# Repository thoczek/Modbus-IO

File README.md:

# Modbus-IO modules<br>

### Complete Modbus I/O modules on ATmega8<br>
### Contains:<br>
 - 4DI-4DO - 4 digital inputs 24VDC and 4 relay NO/NC outputs<br>
 - 8DI - 8 digital inputs 24VDC<br>
 - 7RO - 7 Relay outputs NO/NC<br>
 - WIFI - Module for WIFI conectibity for modules<br>
 - EAP-MODBUSconfig - Software for configuration of the modules.<br>
   Modules have possibility to act in TCP mode throught WIFi module.<br>

### Technology used:
Schematics and PCB board done in Kicad.<br>
Firmware - C++ eclipse. <br>
Software - C#

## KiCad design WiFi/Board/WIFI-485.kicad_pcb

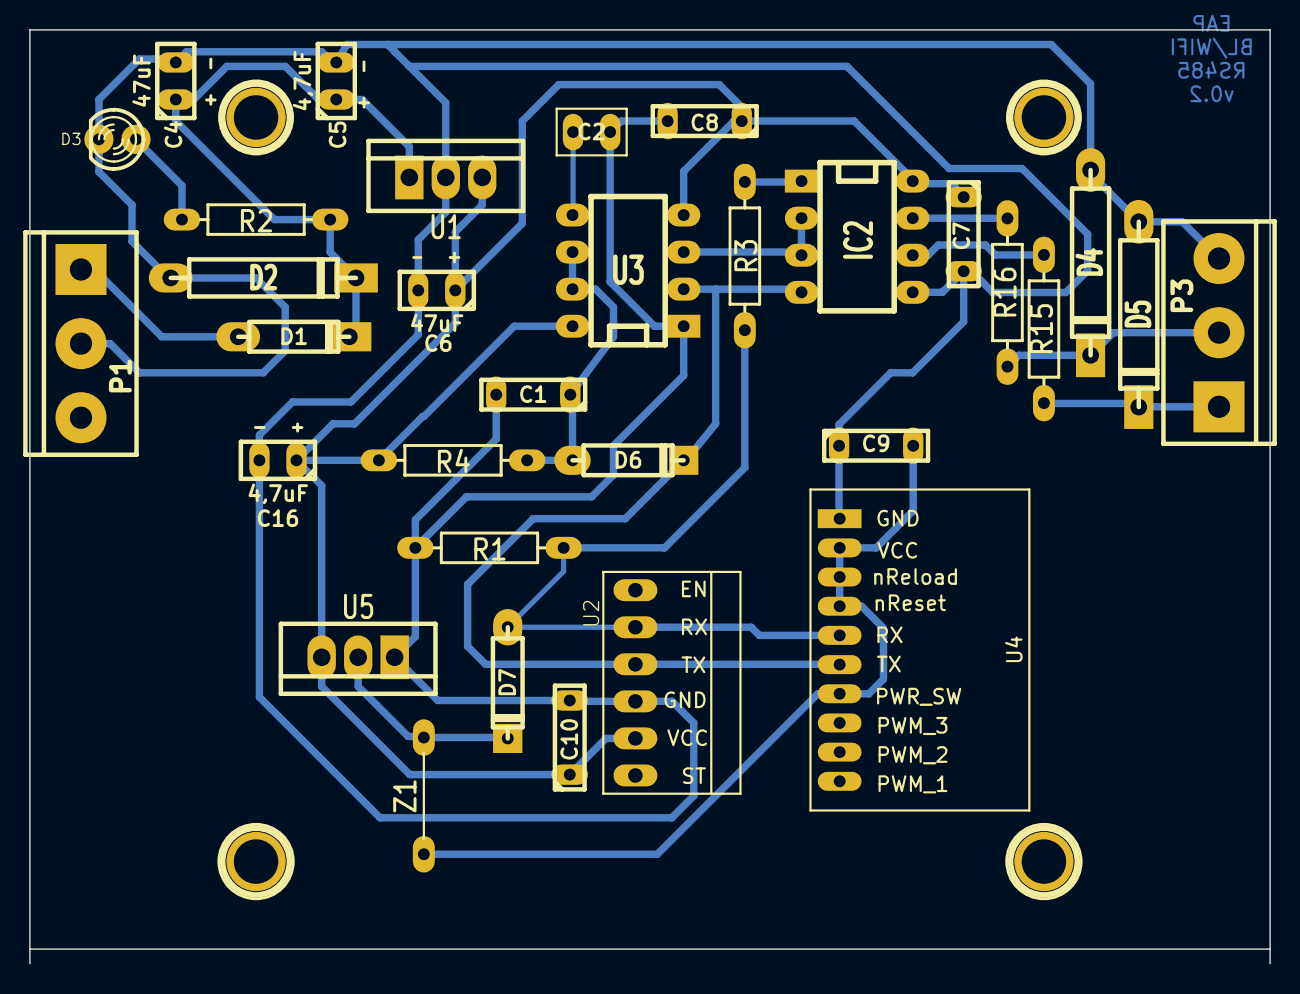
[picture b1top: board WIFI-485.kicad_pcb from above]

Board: 2 copper layers, 85.0 x 64.0 mm, 32 parts (0 on the bottom side), 17 nets.

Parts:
C1: 220nF; C-5
C2: 10nF; C-2_5
C4, C6: 47uF; C-2_5
C5, C16: 4,7uF; C-2_5
C7, C8, C9, C10: 100nF; C-5
D1: DIODE; D3-BOLD
D2: Tr_30V; D5-BOLD
D3: LED; LED-3MM
D4, D5: Tr_15V; D5-BOLD
D6, D7: 1N4148; D3-BOLD
IC2: ADM485; DIP-8__300_ELL
P1, P3: 3_PIN; bornier3
R1: 2k; R-10
R2: 3,9k; R-10
R3: 1_k; R-10
R4: 10k; R-10
R15, R16: 10R; R-10
U1: 7805
U2: HC-05
U3: NE555; DIP-8__300_ELL
U4: USR-WIFI232-T
U5: LD1117V33_; LD1117V33
Z1: Z

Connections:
+5V: C6.1, C7.1, C8.1, C10.1, C16.1, IC2.8, R4.1, U1.VO, U2.2, U3.4, U3.8, U5.3
A: IC2.6, R15.2
B: IC2.7, R16.2
DGND: C1.2, C2.2, C4.2, C5.2, C6.2, C7.2, C8.2, C9.1, C10.2, C16.2, D2.1, D3.2, D4.1, D5.1, IC2.5, P1.2, P3.3, R1.1, U1.GND, U2.3, U3.1, U4.1, U5.1
unnamed: C2.1, U3.5
unnamed: IC2.1, R3.2
unnamed: D6.2, IC2.4, U2.4, U3.2, U4.6
unnamed: IC2.2, IC2.3, U3.3
unnamed: D7.1, R1.2, R3.1, U2.5, U4.5
unnamed: D7.2, U5.2, Z1.1
unnamed: C1.1, D6.1, R4.2, U3.6, U3.7
unnamed: C9.2, U4.2, U4.3, U4.4, U4.7, Z1.2
unnamed: D4.2, P3.2, R16.1
unnamed: D5.2, P3.1, R15.1
unnamed: D1.1, P1.1
unnamed: D3.1, R2.2
VCC: C4.1, C5.1, D1.2, D2.2, R2.1, U1.VI

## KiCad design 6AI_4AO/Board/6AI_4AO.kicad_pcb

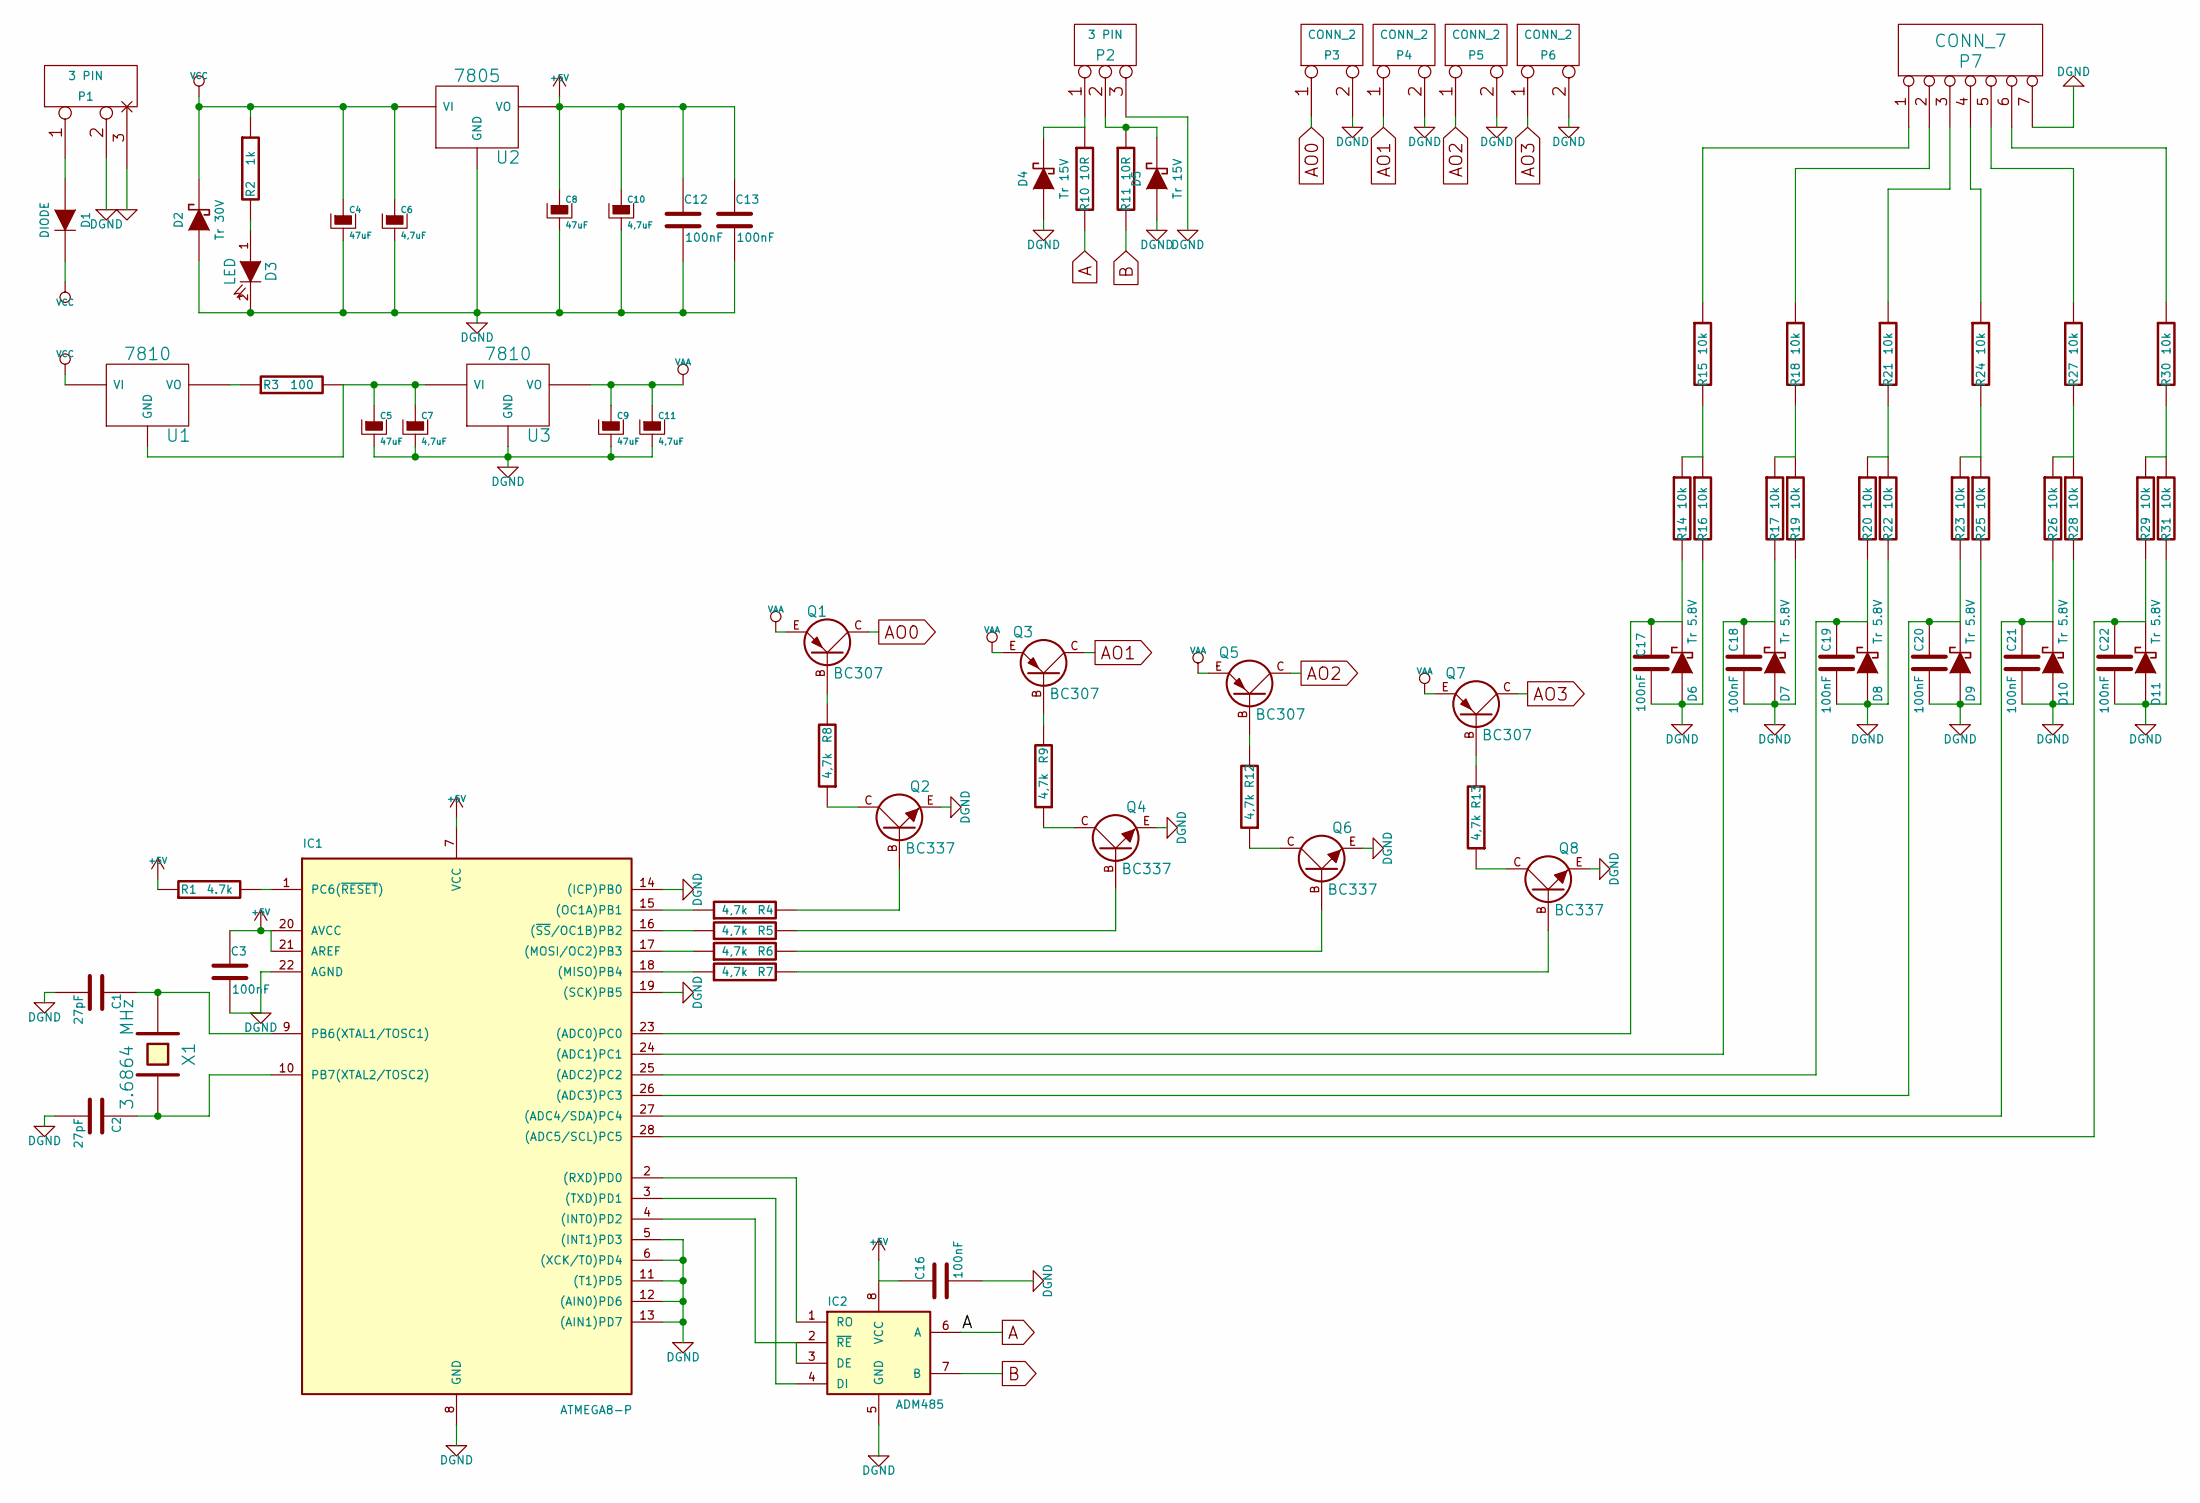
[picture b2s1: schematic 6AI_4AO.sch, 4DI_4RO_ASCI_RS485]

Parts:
C1, C2: 27pF; C-2_5
C3, C12, C13, C16, C17, C18, C19, C20, C21, C22: 100nF; C-5
C4, C5, C8, C9: 47uF; C-2_5
C6, C7, C10, C11: 4,7uF; C-2_5
D1: DIODE; D4-BOLD
D2: Tr 30V; D4-BOLD
D3: LED; LED-3MM
D4, D5: Tr 15V; D4-BOLD
D6, D7, D8, D9, D10, D11: Tr 5.8V; D4-BOLD
IC1: ATMEGA8-P; DIP-28_W7.62mm_LongPads
IC2: ADM485; DIP-8_W7.62mm_LongPads
P1, P2: 3 PIN; bornier3
P3, P4, P5, P6: CONN_2; bornier2
P7: CONN_7; bornier7
Q1, Q3, Q5, Q7: BC307; TO92_Moj
Q2, Q4, Q6, Q8: BC337; TO92_Moj
R1: 4.7k; R-7_62
R2: 1k; R-7_62
R3: 100; R-7_62
R4, R5, R6, R7, R8, R9, R12, R13: 4,7k; R-7_62
R10, R11: 10R; R-7_62
R14, R15, R16, R17, R18, R19, R20, R21, R22, R23, R24, R25, R26, R27, R28, R29, R30, R31: 10k; R-7_62
U1, U3: 7810; 7805
U2: 7805
X1: 3.6864 MHz; Osc_Moj

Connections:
+5V: C3.1, C8.1, C10.1, C12.1, C13.1, C16.1, IC1.7 (VCC), IC1.20 (AVCC), IC1.21 (AREF), IC2.8 (VCC), R1.1, U2.VO
A: IC2.6 (A), R10.2
AO0: P3.1, Q1.C
AO1: P4.1, Q3.C
AO2: P5.1, Q5.C
AO3: P6.1, Q7.C
B: IC2.7 (B), R11.2
DGND: C1.2, C2.2, C3.2, C4.2, C5.2, C6.2, C7.2, C8.2, C9.2, C10.2, C11.2, C12.2, C13.2, C16.2, C17.1, C18.2, C19.2, C20.2, C21.2, C22.2, D2.1 (A), D3.2 (K), D4.1 (A), D5.1 (A), D6.1 (A), D7.1 (A), D8.1 (A), D9.1 (A), D10.1 (A), D11.1 (A), IC1.5 ((INT1)PD3), IC1.6 ((XCK/T0)PD4), IC1.8 (GND), IC1.11 ((T1)PD5), IC1.12 ((AIN0)PD6), IC1.13 ((AIN1)PD7), IC1.14 ((ICP)PB0), IC1.19 ((SCK)PB5), IC1.22 (AGND), IC2.5 (GND), P1.2 (PM), P2.3, P3.2 (PM), P4.2 (PM), P5.2 (PM), P6.2 (PM), P7.7, Q2.E, Q4.E, Q6.E, Q8.E, R16.2, R19.2, R22.2, R25.2, R28.2, R31.2, U2.GND, U3.GND
GND: P1.3 (GND)
unnamed: C1.1, IC1.9 (PB6(XTAL1/TOSC1)), X1.1
unnamed: C2.1, IC1.10 (PB7(XTAL2/TOSC2)), X1.2
unnamed: C5.1, C7.1, R3.2, U1.GND, U3.VI
unnamed: C17.2, D6.2 (K), IC1.23 ((ADC0)PC0), R14.2
unnamed: C18.1, D7.2 (K), IC1.24 ((ADC1)PC1), R17.2
unnamed: C19.1, D8.2 (K), IC1.25 ((ADC2)PC2), R20.2
unnamed: C20.1, D9.2 (K), IC1.26 ((ADC3)PC3), R23.2
unnamed: C21.1, D10.2 (K), IC1.27 ((ADC4/SDA)PC4), R26.2
unnamed: C22.1, D11.2 (K), IC1.28 ((ADC5/SCL)PC5), R29.2
unnamed: D1.1 (A), P1.1
unnamed: D3.1 (A), R2.2
unnamed: D4.2 (K), P2.1, R10.1
unnamed: D5.2 (K), P2.2 (PM), R11.1
unnamed: IC1.1 (PC6(~RESET~)), R1.2
unnamed: IC1.2 ((RXD)PD0), IC2.1 (RO)
unnamed: IC1.3 ((TXD)PD1), IC2.4 (DI)
unnamed: IC1.4 ((INT0)PD2), IC2.2 (~RE~), IC2.3 (DE)
unnamed: IC1.15 ((OC1A)PB1), R4.1
unnamed: IC1.16 ((~SS~/OC1B)PB2), R5.1
unnamed: IC1.17 ((MOSI/OC2)PB3), R6.1
unnamed: IC1.18 ((MISO)PB4), R7.1
unnamed: P7.1, R15.1
unnamed: P7.2, R18.1
unnamed: P7.3, R21.1
unnamed: P7.4, R24.1
unnamed: P7.5, R27.1
unnamed: P7.6, R30.1
unnamed: Q1.B, R8.2
unnamed: Q2.B, R4.2
unnamed: Q2.C, R8.1
unnamed: Q3.B, R9.2
unnamed: Q4.B, R5.2
unnamed: Q4.C, R9.1
unnamed: Q5.B, R12.2
unnamed: Q6.B, R6.2
unnamed: Q6.C, R12.1
unnamed: Q7.B, R13.2
unnamed: Q8.B, R7.2
unnamed: Q8.C, R13.1
unnamed: R3.1, U1.VO
unnamed: R14.1, R15.2, R16.1
unnamed: R17.1, R18.2, R19.1
unnamed: R20.1, R21.2, R22.1
unnamed: R23.1, R24.2, R25.1
unnamed: R26.1, R27.2, R28.1
unnamed: R29.1, R30.2, R31.1
VAA: C9.1, C11.1, Q1.E, Q3.E, Q5.E, Q7.E, U3.VO
VCC: C4.1, C6.1, D1.2 (K), D2.2 (K), R2.1, U1.VI, U2.VI

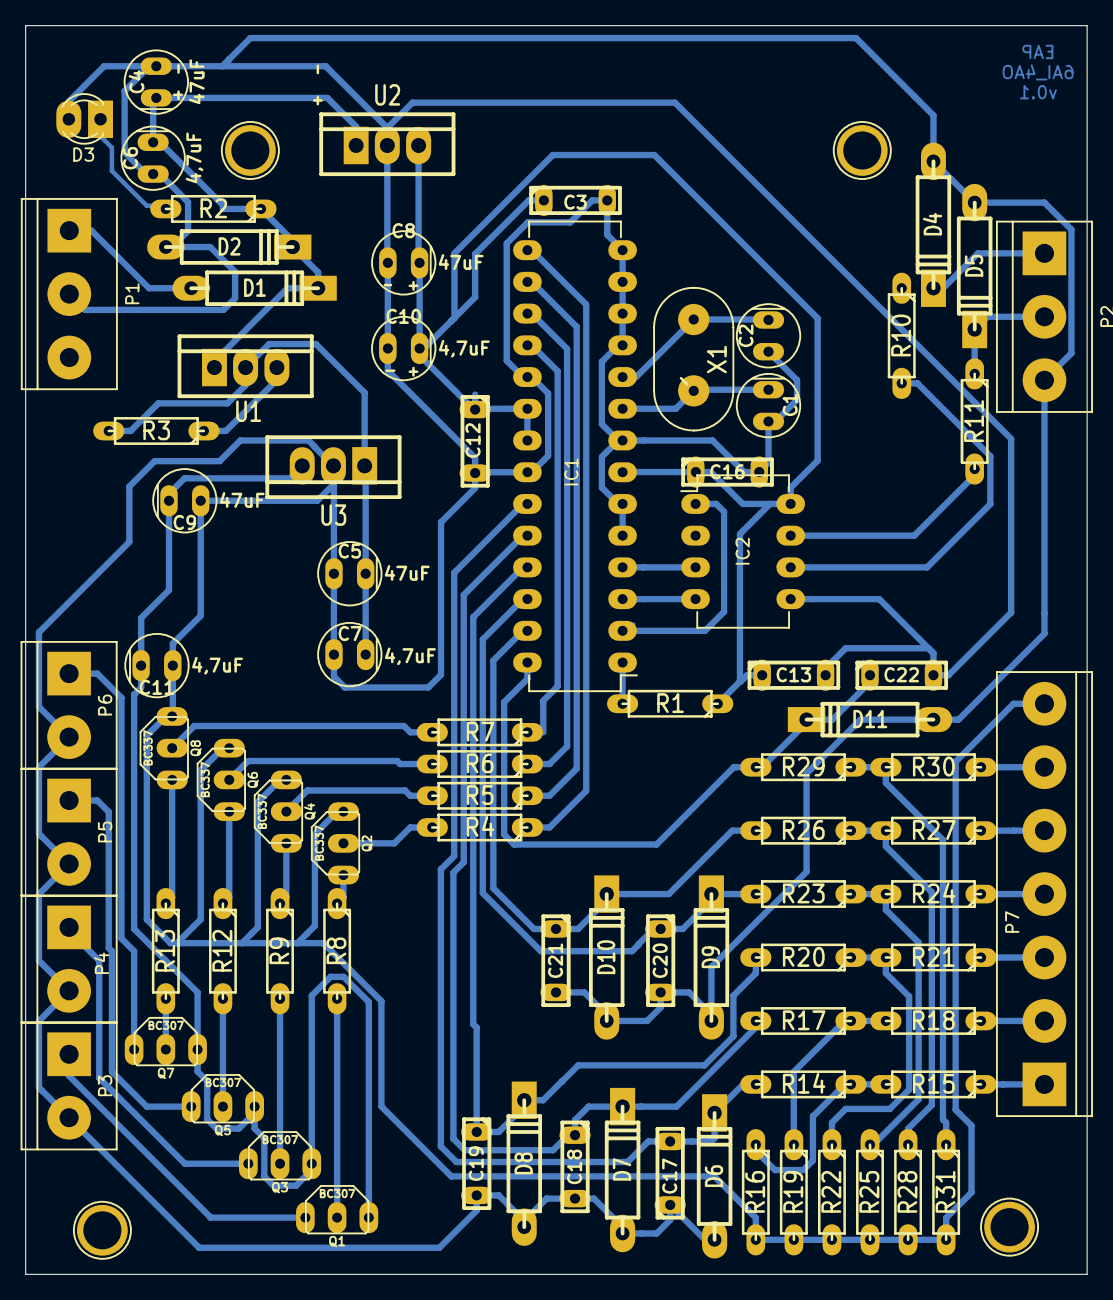
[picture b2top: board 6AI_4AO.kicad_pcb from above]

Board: 2 copper layers, 85.0 x 100.0 mm, 83 parts (0 on the bottom side), 56 nets.

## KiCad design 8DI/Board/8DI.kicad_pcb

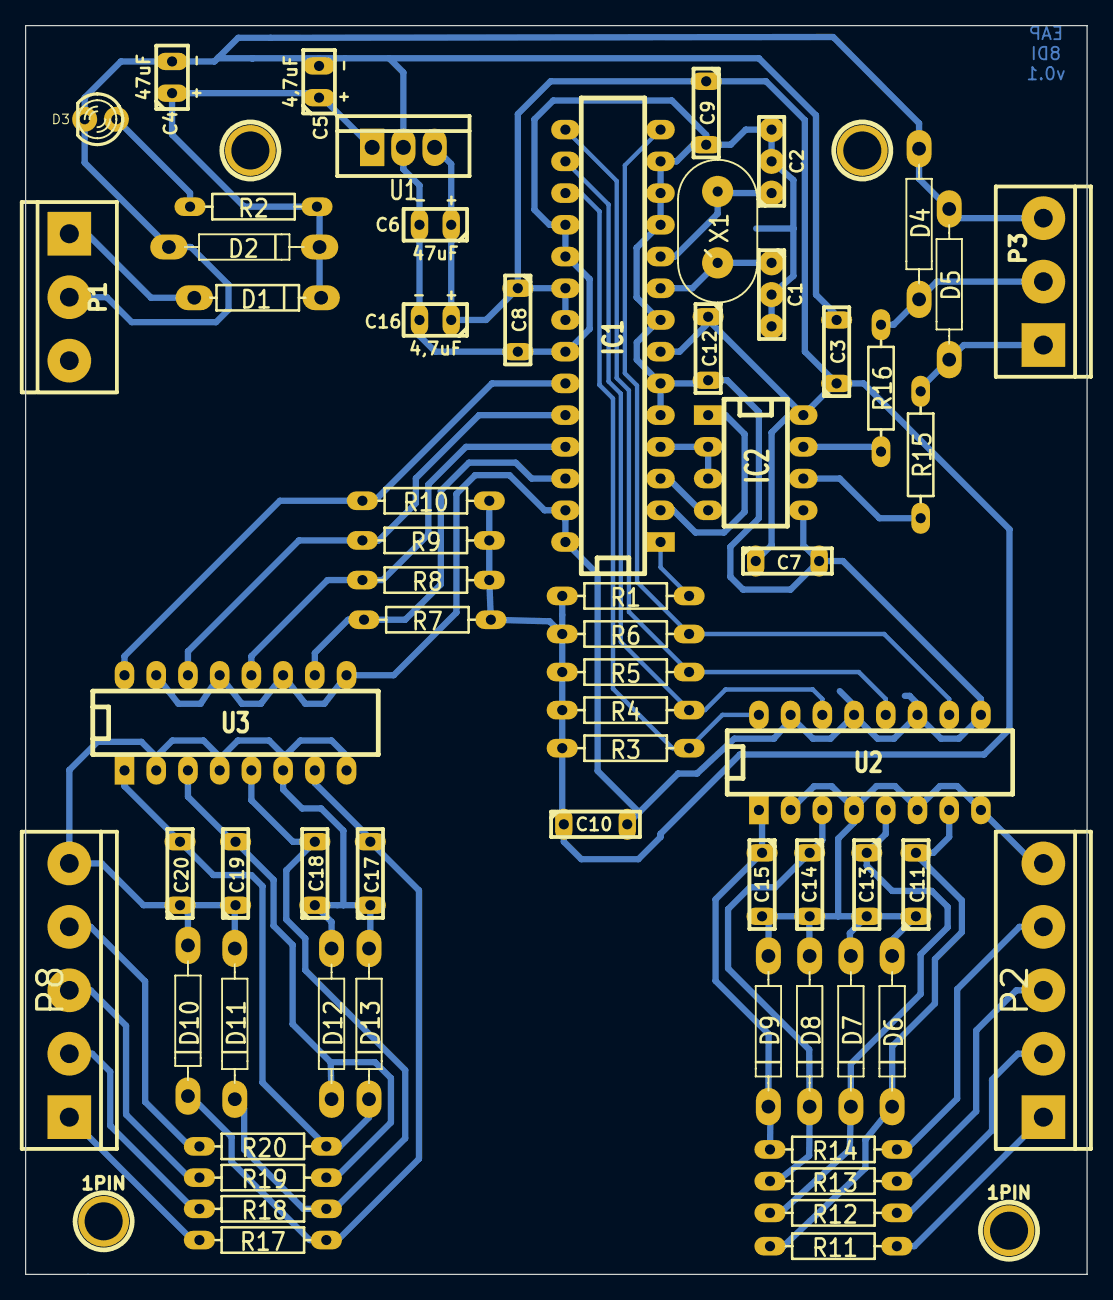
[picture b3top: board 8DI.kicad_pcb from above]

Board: 2 copper layers, 85.0 x 100.0 mm, 65 parts (0 on the bottom side), 40 nets.

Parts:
1PIN, 1PIN#2: P***; 1pin
C1, C2: C; C1-1
C3, C7, C8, C9, C10, C11, C12, C13, C14, C15, C17, C18, C19, C20: 100nF; C-5
C4, C6: 47uF; C-2_5
C5, C16: 4,7uF; C-2_5
D1: R-10
D2, D4, D5, D6, D7, D8, D9, D10, D11, D12, D13: R-12
D3: LED-3MM
IC1: ATMEGA8-P; DIP-28__300_ELL
IC2: DIP-8__300_ELL
P1, P3: bornier3
P2, P8: bornier5
R1, R2, R3, R4, R5, R6, R7, R8, R9, R10, R11, R12, R13, R14, R15, R16, R17, R18, R19, R20: R-10
U1: 7805
U2, U3: DIP-16__300_ELL
X1: Osc_Moj

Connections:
+5V: C3.1, C6.1, C7.1, C8.1, C9.1, C10.1, C12.1, C16.1, IC1.7, IC1.20, IC1.21, IC2.8, R1.1, R3.1, R4.1, R5.1, R6.1, R7.2, R8.2, R9.2, R10.2, U1.VO
A: IC2.6, R15.2
B: IC2.7, R16.2
DGND: C1.2, C2.2, C3.2, C4.2, C5.2, C6.2, C7.2, C8.2, C9.2, C10.2, C12.2, C16.2, D2.1, D3.2, D4.1, D5.1, IC1.5, IC1.6, IC1.8, IC1.11, IC1.12, IC1.13, IC1.18, IC1.19, IC1.22, IC1.27, IC1.28, IC2.5, P1.2, P3.3, U1.GND, U2.9, U2.11, U2.13, U2.15, U3.9, U3.11, U3.13, U3.15
GNDPWR: C11.1, C13.2, C14.2, C15.2, C17.1, C18.1, C19.1, C20.1, D6.1, D7.1, D8.1, D9.1, D10.1, D11.1, D12.1, D13.1, P2.5, P8.5, U2.2, U2.4, U2.6, U2.8, U3.2, U3.4, U3.6, U3.8
unnamed: P2.2, R12.1
unnamed: D5.2, P3.1, R15.1
unnamed: IC1.4, IC2.2, IC2.3
unnamed: D1.1, P1.1
unnamed: D3.1, R2.2
unnamed: P2.1, R11.1
unnamed: IC1.2, IC2.1
unnamed: IC1.3, IC2.4
unnamed: P2.3, R13.1
unnamed: P2.4, R14.1
unnamed: P8.2, R18.2
unnamed: P8.3, R19.2
unnamed: P8.4, R20.2
unnamed: IC1.24, R9.1, U3.14
unnamed: C20.2, D13.2, R20.1, U3.1
unnamed: IC1.25, R8.1, U3.12
unnamed: P8.1, R17.2
unnamed: C17.2, D10.2, R17.1, U3.7
unnamed: C18.2, D11.2, R18.1, U3.5
unnamed: C19.2, D12.2, R19.1, U3.3
unnamed: IC1.26, R7.1, U3.10
unnamed: C14.1, D8.2, R13.2, U2.3
unnamed: C15.1, D9.2, R14.2, U2.1
unnamed: C1.1, IC1.9, X1.1
unnamed: C2.1, IC1.10, X1.2
unnamed: C11.2, D6.2, R11.2, U2.7
unnamed: C13.1, D7.2, R12.2, U2.5
unnamed: IC1.23, R10.1, U3.16
unnamed: IC1.1, R1.2
unnamed: IC1.17, R3.2, U2.16
unnamed: IC1.14, R6.2, U2.10
unnamed: IC1.15, R5.2, U2.12
unnamed: IC1.16, R4.2, U2.14
unnamed: D4.2, P3.2, R16.1
VCC: C4.1, C5.1, D1.2, D2.2, R2.1, U1.VI

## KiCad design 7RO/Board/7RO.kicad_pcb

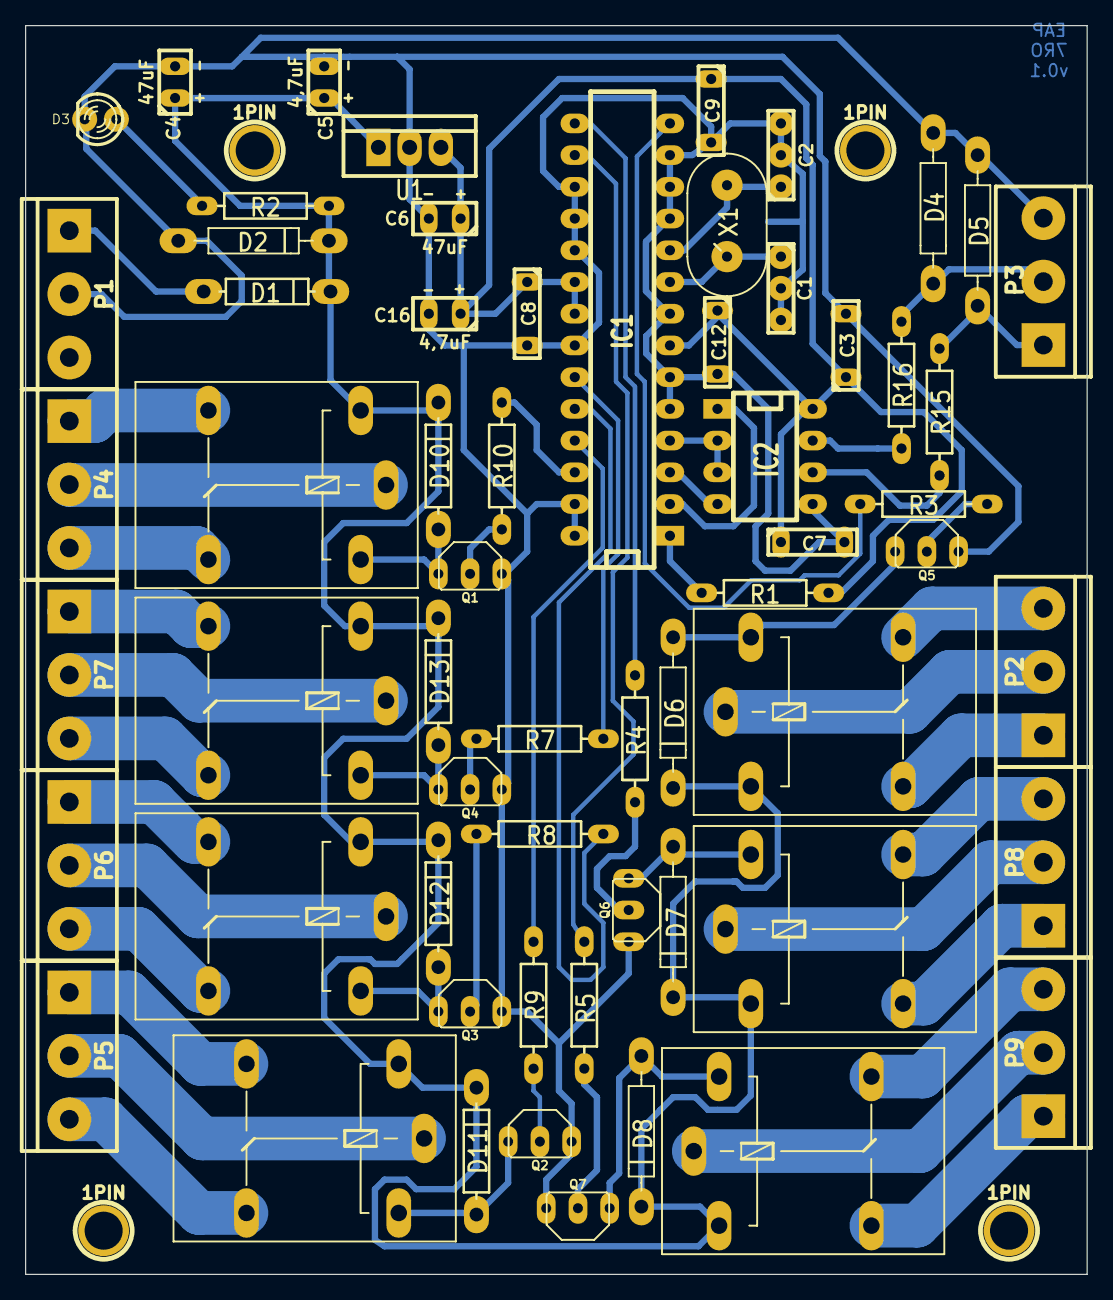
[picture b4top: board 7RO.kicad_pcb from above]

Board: 2 copper layers, 85.0 x 100.0 mm, 65 parts (0 on the bottom side), 57 nets.

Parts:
1PIN, 1PIN#2, 1PIN#3, 1PIN#4: P***; 1pin
C1, C2: C; C1-1
C3, C7, C8, C9, C12: 100nF; C-5
C4, C6: 47uF; C-2_5
C5, C16: 4,7uF; C-2_5
D1: R-10
D2, D4, D5, D6, D7, D8: R-12
D3: LED; LED-3MM
D10, D11, D12, D13: DIODE; R-10
IC1: ATMEGA8-P; DIP-28__300_ELL
IC2: DIP-8__300_ELL
K1, K2, K3, K4, K5, K6, K7: relay-G5LE
P1: CONN_PWR; bornier3
P2, P3, P4, P5, P6, P7, P8, P9: bornier3
Q1, Q2, Q3, Q4, Q5, Q6, Q7: BC337; TO92_Moj
R1: 4.7k; R-10
R2: 3k; R-10
R3, R4, R5, R15, R16: R-10
R7, R8, R9, R10: 450; R-10
U1: 7805
X1: CRYSTAL; Osc_Moj

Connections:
+5V: C3.1, C6.1, C7.1, C8.1, C9.1, C12.1, C16.1, IC1.7, IC1.20, IC1.21, IC2.8, R1.1, U1.VO
A: IC2.6, R15.2
B: IC2.7, R16.2
DGND: C1.2, C2.2, C3.2, C4.2, C5.2, C6.2, C7.2, C8.2, C9.2, C12.2, C16.2, D2.1, D3.2, D4.1, D5.1, IC1.5, IC1.6, IC1.8, IC1.11, IC1.12, IC1.13, IC1.17, IC1.18, IC1.19, IC1.22, IC1.27, IC1.28, IC2.5, P1.2, P3.3, Q1.E, Q2.E, Q3.E, Q4.E, Q5.E, Q6.E, Q7.E, U1.GND
unnamed: K2.P, P5.2
unnamed: K1.O, P4.3
unnamed: K1.S, P4.1
unnamed: K1.P, P4.2
unnamed: K2.S, P5.1
unnamed: D10.1, K1.2, Q1.C
unnamed: K4.P, P7.2
unnamed: D5.2, P3.1, R15.1
unnamed: K4.S, P7.1
unnamed: K4.O, P7.3
unnamed: K3.S, P6.1
unnamed: K3.O, P6.3
unnamed: K3.P, P6.2
unnamed: K2.O, P5.3
unnamed: D3.1, R2.2
unnamed: D1.1, P1.1
unnamed: IC1.4, IC2.2, IC2.3
unnamed: IC1.3, IC2.4
unnamed: IC1.2, IC2.1
unnamed: D11.1, K2.2, Q2.C
unnamed: D12.1, K3.2, Q3.C
unnamed: D13.1, K4.2, Q4.C
unnamed: K7.P, P9.2
unnamed: Q5.B, R3.1
unnamed: Q7.B, R5.1
unnamed: Q6.B, R4.1
unnamed: K6.S, P8.1
unnamed: K7.S, P9.1
unnamed: K7.O, P9.3
unnamed: K6.O, P8.3
unnamed: K5.O, P2.3
unnamed: K5.S, P2.1
unnamed: K6.P, P8.2
unnamed: K5.P, P2.2
unnamed: IC1.16, R5.2
unnamed: IC1.15, R4.2
unnamed: IC1.14, R3.2
unnamed: D8.1, K7.2, Q7.C
unnamed: D7.1, K6.2, Q6.C
unnamed: D6.1, K5.2, Q5.C
unnamed: Q1.B, R10.1
unnamed: Q3.B, R8.1
unnamed: Q2.B, R9.1
unnamed: Q4.B, R7.1
unnamed: IC1.26, R10.2
unnamed: IC1.25, R9.2
unnamed: IC1.24, R8.2
unnamed: IC1.23, R7.2
unnamed: C2.1, IC1.10, X1.2
unnamed: C1.1, IC1.9, X1.1
unnamed: IC1.1, R1.2
unnamed: D4.2, P3.2, R16.1
VCC: C4.1, C5.1, D1.2, D2.2, D6.2, D7.2, D8.2, D10.2, D11.2, D12.2, D13.2, K1.1, K2.1, K3.1, K4.1, K5.1, K6.1, K7.1, R2.1, U1.VI
